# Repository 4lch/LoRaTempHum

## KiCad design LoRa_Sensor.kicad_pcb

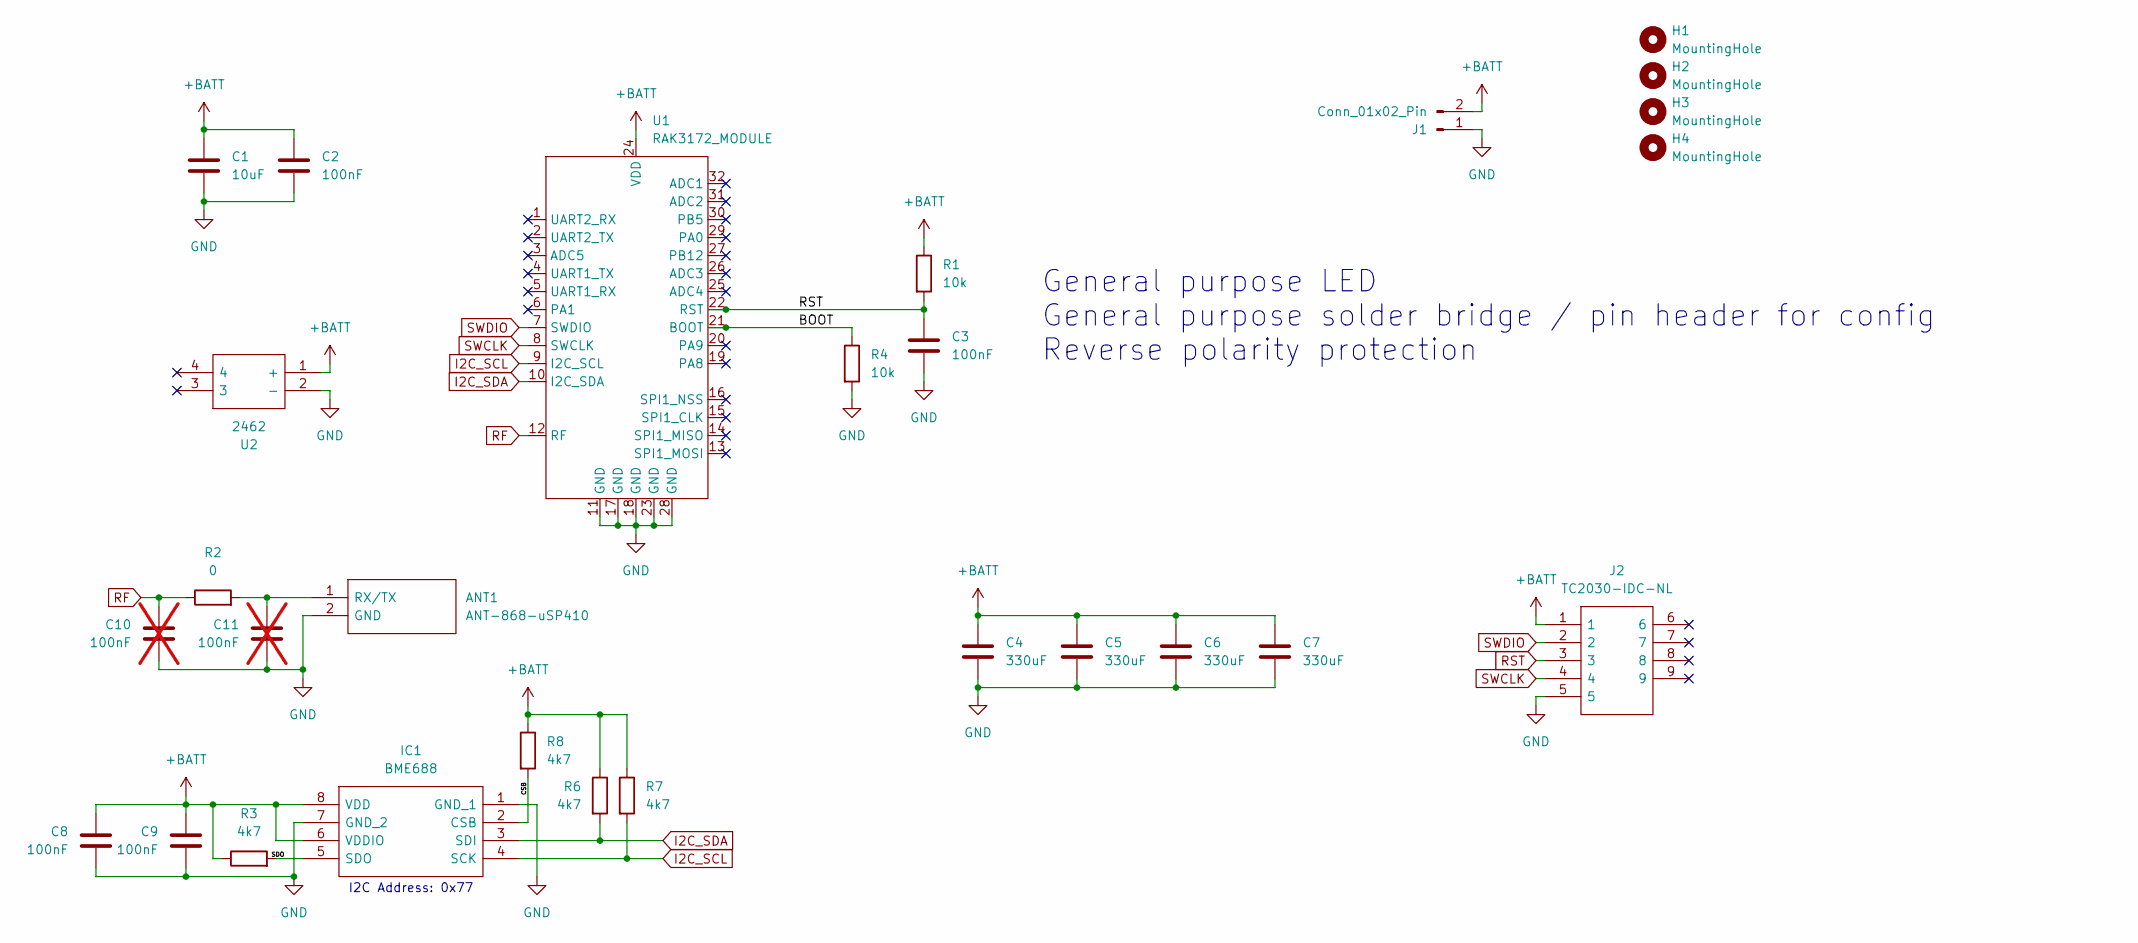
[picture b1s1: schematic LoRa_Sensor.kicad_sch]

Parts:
ANT1: ANT-868-uSP410; ANT868uSP410; Manufacturer_Part_Number ANT-868-uSP410; Mouser Part Number 712-ANT-868-USP410
C1: 10uF; C_0603_1608Metric
C2, C3, C8, C9: 100nF; C_0603_1608Metric
C4, C5, C6, C7: 330uF; CP_EIA-3528-15_AVX-H
C10, C11: 100nF; C_0603_1608Metric; not fitted
H1, H2, H3, H4: MountingHole; MountingHole_3.2mm_M3
IC1: BME688; Mouser Part Number 262-BME688
J1: Conn_01x02_Pin; PinHeader_1x02_P2.54mm_Vertical
J2: TC2030-IDC-NL; TC2030IDCNL; Manufacturer_Part_Number TC2030-IDC-NL
R1, R4: 10k; R_0805_2012Metric
R2: 0; R_0603_1608Metric
R3, R6, R7, R8: 4k7; R_0805_2012Metric
U1: RAK3172_MODULE
U2: 2462; Mouser Part Number 534-2462

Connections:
+BATT: C1.1, C2.1, C4.1, C5.1, C6.1, C7.1, C8.1, C9.1, IC1.6 (VDDIO), IC1.8 (VDD), J1.2, J2.1, R1.1, R3.1, R6.1, R7.1, R8.1, U1.24 (VDD), U2.1 (+)
/BOOT: R4.1, U1.21 (BOOT)
/CSB: IC1.2 (CSB), R8.2
/SDO: IC1.5 (SDO), R3.2
GND: ANT1.2 (GND), C1.2, C2.2, C3.2, C4.2, C5.2, C6.2, C7.2, C8.2, C9.2, C10.2, C11.2, IC1.1 (GND_1), IC1.7 (GND_2), J1.1, J2.5, R4.2, U1.11 (GND), U1.17 (GND), U1.18 (GND), U1.23 (GND), U1.28 (GND), U2.2 (-)
I2C_SCL: IC1.4 (SCK), R7.2, U1.9 (I2C_SCL)
I2C_SDA: IC1.3 (SDI), R6.2, U1.10 (I2C_SDA)
unnamed: ANT1.1 (RX/TX), C11.1, R2.2
RF: C10.1, R2.1, U1.12 (RF)
RST: C3.1, J2.3, R1.2, U1.22 (RST)
SWCLK: J2.4, U1.8 (SWCLK)
SWDIO: J2.2, U1.7 (SWDIO)

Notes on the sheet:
I2C Address: 0x77
General purpose LED General purpose solder bridge / pin header for config Reverse polarity protection

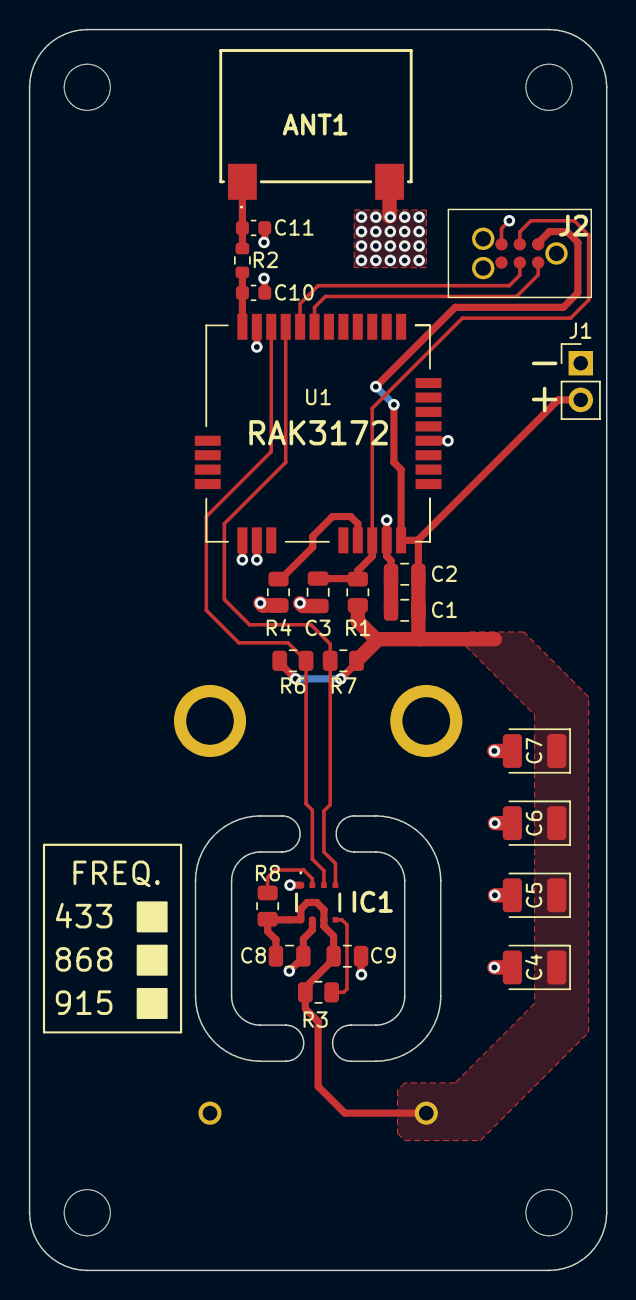
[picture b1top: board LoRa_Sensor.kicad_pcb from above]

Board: 2 copper layers, 40.0 x 86.0 mm, 28 parts (1 on the bottom side), 12 nets.

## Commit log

2023-11-22 v0.2 en cours
2023-11-22 done for the day :)
2023-11-24 add checkboxes for frequency
